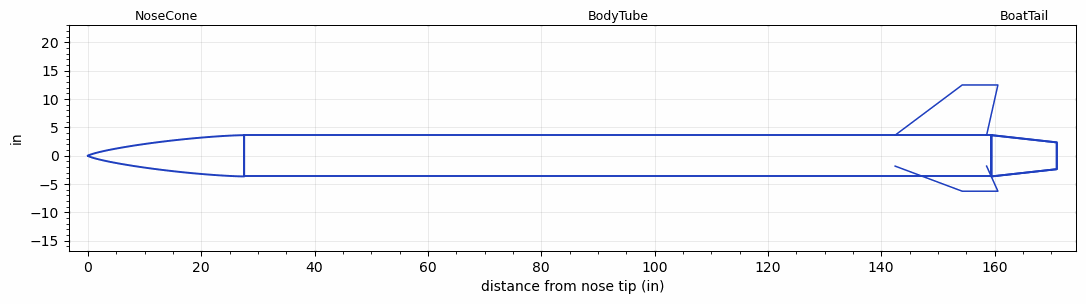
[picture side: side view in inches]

<RASAeroDocument>
 <FileVersion>2</FileVersion>
 <RocketDesign>
  <NoseCone>
   <Length>27.56</Length>
   <Diameter>7.283</Diameter>
   <Shape>Von Karman Ogive</Shape>
   <Location>0</Location>
  </NoseCone>
  <BodyTube>
   <Length>131.9</Length>
   <Diameter>7.283</Diameter>
   <Location>27.56</Location>
   <BoattailLength>11.532</BoattailLength>
   <BoattailRearDiameter>4.7244</BoattailRearDiameter>
   <Fin>
    <Count>3</Count>
    <Chord>16.147</Chord>
    <Span>8.8583</Span>
    <SweepDistance>11.84</SweepDistance>
    <TipChord>6.3</TipChord>
    <Thickness>0.2362</Thickness>
    <Location>17</Location>
    <AirfoilSection>Hexagonal</AirfoilSection>
    <FX1>1</FX1>
    <FX3>1</FX3>
   </Fin>
   <Protuberance>
    <StreamlinedNoBaseDrag>1.5</StreamlinedNoBaseDrag>
    <StreamlinedWithBaseDrag>1.94</StreamlinedWithBaseDrag>
    <InclinedPlate1Angle>0</InclinedPlate1Angle>
    <InclinedPlate1FrontalArea>0</InclinedPlate1FrontalArea>
    <InclinedPlate2Angle>0</InclinedPlate2Angle>
    <InclinedPlate2FrontalArea>0</InclinedPlate2FrontalArea>
   </Protuberance>
  </BodyTube>
  <BoatTail>
   <Length>11.532</Length>
   <Diameter>7.283</Diameter>
   <RearDiameter>4.7244</RearDiameter>
   <Location>159.46</Location>
  </BoatTail>
  <Surface>Smooth Paint</Surface>
  <ModifiedBarrowman>False</ModifiedBarrowman>
  <Turbulence>False</Turbulence>
  <UseBooster1>False</UseBooster1>
  <UseBooster2>False</UseBooster2>
 </RocketDesign>
 <LaunchSite>
  <Altitude>0</Altitude>
  <Pressure>0</Pressure>
  <RodAngle>6</RodAngle>
  <RodLength>39</RodLength>
  <Temperature>74</Temperature>
  <WindSpeed>9.46</WindSpeed>
 </LaunchSite>
 <Recovery>
  <Altitude1>1000</Altitude1>
  <Altitude2>1500</Altitude2>
  <DeviceType1>Parachute</DeviceType1>
  <DeviceType2>Parachute</DeviceType2>
  <Event1>True</Event1>
  <Event2>True</Event2>
  <Size1>43</Size1>
  <Size2>120</Size2>
  <EventType1>Apogee</EventType1>
  <EventType2>Altitude</EventType2>
  <CD1>1.33</CD1>
  <CD2>1.33</CD2>
 </Recovery>
 <SimulationList>
  <Simulation>
   <SustainerEngine>RL155  (ICLR)</SustainerEngine>
   <SustainerLaunchWt>174</SustainerLaunchWt>
   <SustainerNozzleDiameter>3.54</SustainerNozzleDiameter>
   <SustainerCG>99.61</SustainerCG>
   <SustainerIgnitionDelay>0</SustainerIgnitionDelay>
   <Booster1SeparationDelay>0</Booster1SeparationDelay>
   <Booster1IgnitionDelay>0</Booster1IgnitionDelay>
   <IncludeBooster1>False</IncludeBooster1>
   <Booster2Delay>0</Booster2Delay>
   <IncludeBooster2>False</IncludeBooster2>
   <TimetoApogee>42.16893</TimetoApogee>
   <MaxAltitude>27855.02</MaxAltitude>
   <MaxVelocity>1624.613</MaxVelocity>
  </Simulation>
 </SimulationList>
</RASAeroDocument>
